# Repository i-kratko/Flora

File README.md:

# Flora
![Logo
](https://github.com/i-kratko/Flora/blob/main/Media/Flora_Project_Logo.png)

Flora is an IoT project developed during my internship in Smartcom  AD. It is a plant monitoring system that keeps track of parameters such as air humidity and soil Bulgariamoisture and displays information on a Grafana dashboard.

# Блок схема

# Блок схема код

# Принципна електрическа схема
![Electrircal scheme
](https://github.com/i-kratko/Flora/blob/main/Media/Flora_Schematic.png)

# Дизайн на платката
![PCB
](https://github.com/i-kratko/Flora/blob/main/Media/Flora_PCB_Design.png)

![PCB
](https://github.com/i-kratko/Flora/blob/main/Media/Flora_PCB_1.png)

![PCB
](https://github.com/i-kratko/Flora/blob/main/Media/Flora_PCB_2.png)

![PCB
](https://github.com/i-kratko/Flora/blob/main/Media/Flora_PCB_3.png)

![PCB
](https://github.com/i-kratko/Flora/blob/main/Media/Flora_PCB_4.png)

# Документация

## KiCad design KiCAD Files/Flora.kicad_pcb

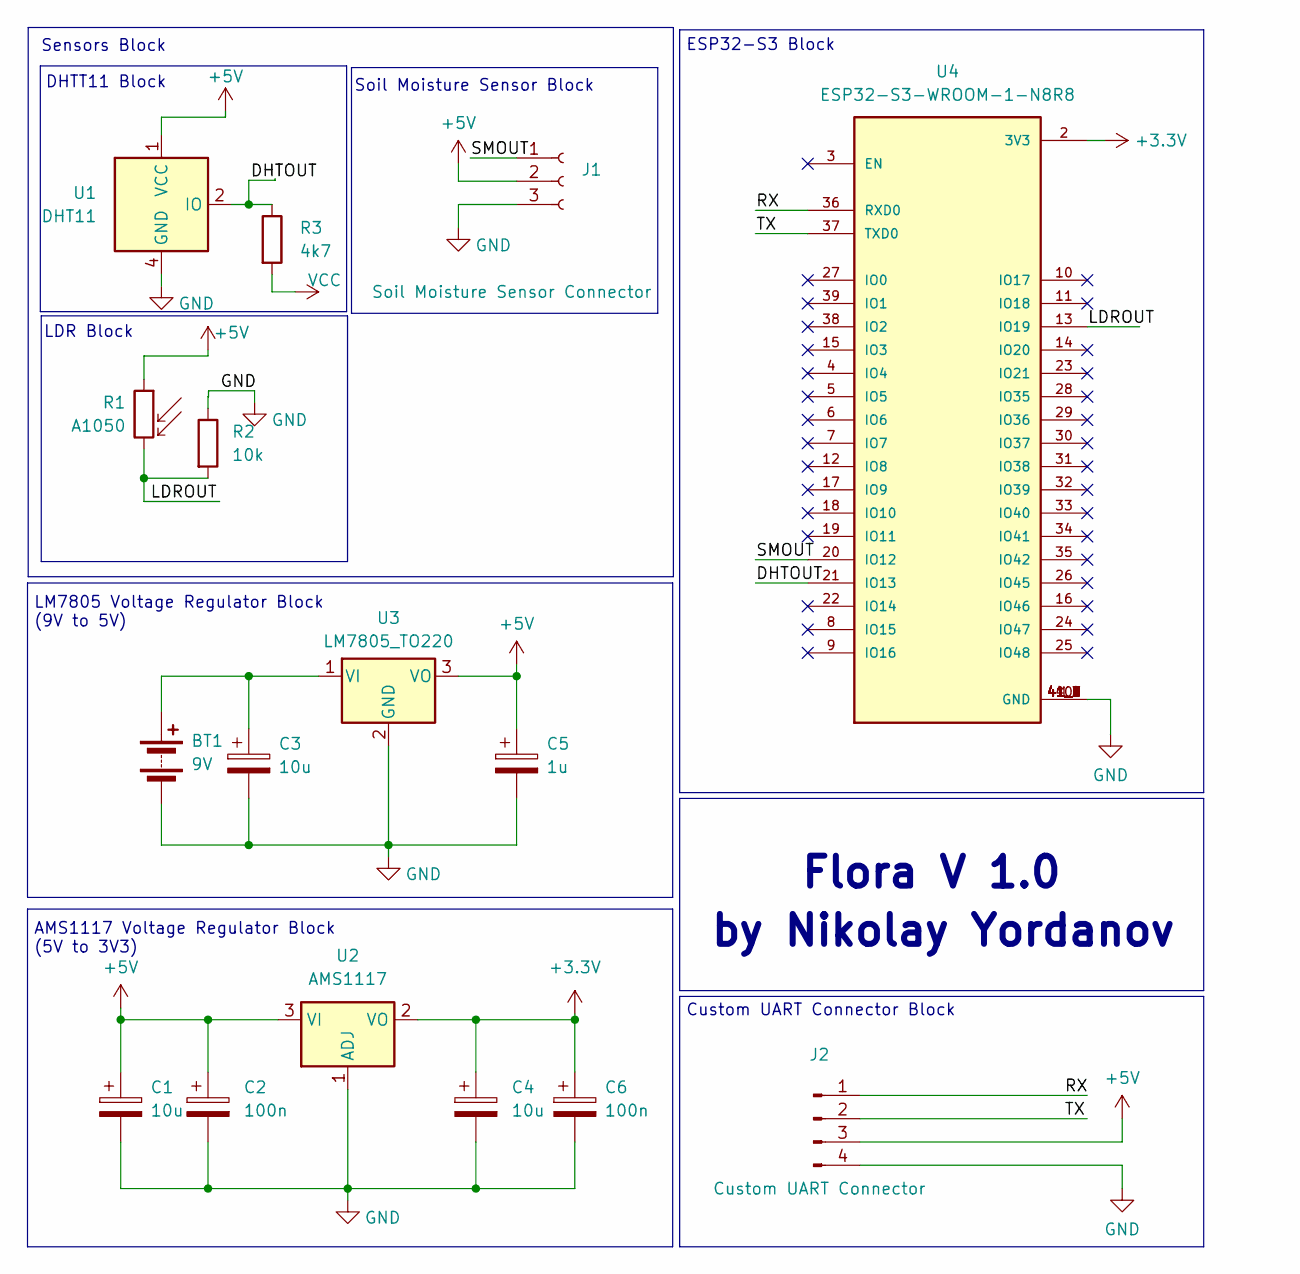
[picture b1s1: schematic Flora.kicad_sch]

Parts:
BT1: 9V; TerminalBlock_Altech_AK300-2_P5.00mm
C1, C3, C4: 10u; C_0201_0603Metric
C2, C6: 100n; C_0201_0603Metric
C5: 1u; C_0201_0603Metric
J1: Soil Moisture Sensor Connector; PinSocket_1x03_P2.54mm_Vertical
J2: Custom UART Connector; PinHeader_1x04_P2.54mm_Vertical
R1: A1050; R_LDR_D6.4mm_P3.4mm_Vertical
R2: 10k; R_0402_1005Metric_Pad0.72x0.64mm_HandSolder
R3: 4k7; R_0402_1005Metric_Pad0.72x0.64mm_HandSolder
U1: DHT11; Aosong_DHT11_5.5x12.0_P2.54mm
U2: AMS1117; SOT-223-3_TabPin2
U3: LM7805_TO220; TO-220-3_Vertical
U4: ESP32-S3-WROOM-1-N8R8; XCVR_ESP32S3WROOM1N8R8

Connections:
+3.3V: C4.1, C6.1, U2.2 (VO), U4.2 (3V3)
+5V: C1.1, C2.1, C5.1, J1.2, J2.3, R1.1, U1.1 (VCC), U2.3 (VI), U3.3 (VO)
/DHTOUT: R3.1, U1.2 (IO), U4.21 (IO13)
/LDROUT: R1.2, R2.2, U4.13 (IO19)
/RX: J2.1, U4.36 (RXD0)
/SMOUT: J1.1, U4.20 (IO12)
/TX: J2.2, U4.37 (TXD0)
GND: BT1.2 (-), C1.2, C2.2, C3.2, C4.2, C5.2, C6.2, J1.3, J2.4, R2.1, U1.4 (GND), U2.1 (ADJ), U3.2 (GND), U4.1 (GND), U4.40 (GND), U4.41_1 (GND), U4.41_2 (GND), U4.41_3 (GND), U4.41_4 (GND), U4.41_5 (GND), U4.41_6 (GND), U4.41_7 (GND), U4.41_8 (GND), U4.41_9 (GND)
unnamed: BT1.1 (+), C3.1, U3.1 (VI)
VCC: R3.2

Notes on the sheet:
LDR Block
Sensors Block
Flora V 1.0
Custom UART Connector Block
ESP32-S3 Block
DHTT11 Block
by Nikolay Yordanov
Soil Moisture Sensor Block
AMS1117 Voltage Regulator Block (5V to 3V3)
LM7805 Voltage Regulator Block (9V to 5V)

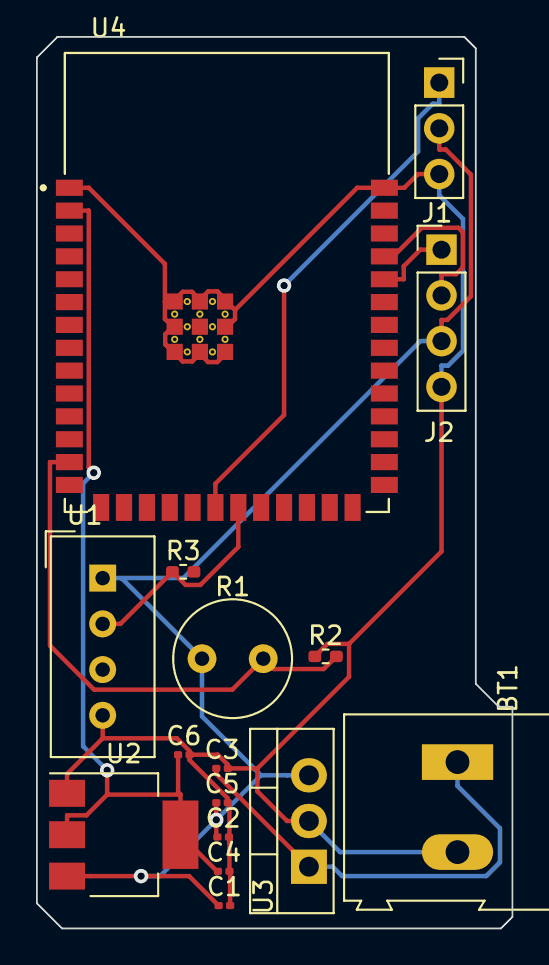
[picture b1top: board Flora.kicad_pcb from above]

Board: 2 copper layers, 26.4 x 49.5 mm, 16 parts (0 on the bottom side), 9 nets.

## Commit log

2023-07-11 Added KiCAD Project Files
2023-07-12 Add Folder
2023-07-12 Added code
2023-07-12 Logo
2023-07-12 More Media
2023-07-12 logo change
